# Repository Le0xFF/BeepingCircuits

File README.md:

# Beeping Circuits

Just a bunch of beeping circuits I made for fun.

Moved to Codeberg: https://codeberg.org/Le0xFF/BeepingCircuits

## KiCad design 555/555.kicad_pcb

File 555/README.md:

# 555

A beeping circuit made with a 555 IC.

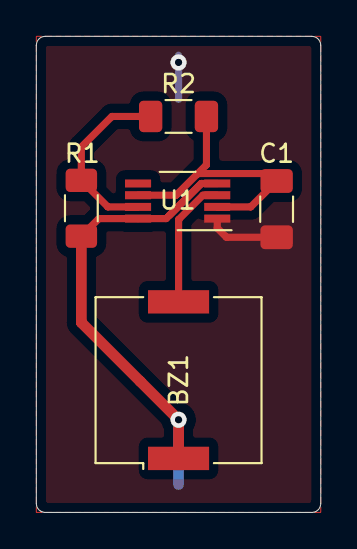
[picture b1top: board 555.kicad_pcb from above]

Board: 2 copper layers, 15.8 x 26.4 mm, 6 parts (1 on the bottom side), 5 nets.

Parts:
BT1: S8421-45R; BatteryHolder
BZ1: Buzzer; Buzzer_Murata_PKMCS0909E4000-R1
C1: 100 uF; C_1206_3216Metric_Pad1.33x1.80mm_HandSolder
R1: 4.7 MOhm; R_1206_3216Metric_Pad1.30x1.75mm_HandSolder
R2: 1 kOhm; R_1206_3216Metric_Pad1.30x1.75mm_HandSolder
U1: TLC555xPS; VSSOP-8_3.0x3.0mm_P0.65mm

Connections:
/VCC: BT1.2, BZ1.1, R1.1, U1.4, U1.8
GND: BT1.1, C1.2, U1.1
unnamed: BZ1.2, U1.3
unnamed: C1.1, R2.2, U1.2, U1.6
unnamed: R1.2, R2.1, U1.7

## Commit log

2022-01-05 Files upload
